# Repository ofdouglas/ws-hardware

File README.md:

# WireSpaces hardware

Status: draft · Owner: project maintainer · Updated: 2026-09-06

Hardware experiments for WireSpaces (WS), starting with a small four-MCU bench board. This repository is a design scaffold, not a fabrication release. Board1 has a complete draft KiCad schematic, reconciled counts and [initial unrouted PCB placement](boards/board1/kicad/placement.md). Schematic approval, detailed placement/routing and hardware qualification remain. This is not a validated fabrication or ordering package.

## Start here

1. Read [agent instructions](AGENTS.md) and [document/decision conventions](docs/DESIGN_PRINCIPLES.md).
2. Read [system context](docs/WIRESPACES_SYSTEM_CONTEXT.md) and [family architecture](docs/HARDWARE_ARCHITECTURE.md).
3. Check the [ADR index](docs/decisions/README.md) before changing a decision.
4. Work from [Board 1 requirements](boards/board1/requirements.md), then its [current design overview](boards/board1/README.md), [pinmap](boards/board1/pinmap.md) and [BOM](boards/board1/bom_internal.csv).

```text
ws-hardware/
├── AGENTS.md
├── README.md
├── docs/
│   ├── WIRESPACES_SYSTEM_CONTEXT.md
│   ├── HARDWARE_ARCHITECTURE.md
│   ├── DESIGN_PRINCIPLES.md
│   ├── PART_SELECTION_POLICY.md
│   ├── SOURCE_NOTES.md
│   └── decisions/                 # index, template, numbered ADRs
├── boards/board1/
│   ├── README.md
│   ├── requirements.md
│   ├── pinmap.md
│   ├── bom_internal.csv
│   └── kicad/                    # board CAD workspace; see board status
└── libraries/
    ├── symbols/
    └── footprints/
```

Board 1's Rev A networking scope has one STM32 gateway, three SAM leaves, two shared CAN-FD buses, an onboard multidrop UART, a private SAM UART ring, USB power/VCP, one external RS-485, signal terminals for both CANs and RS-485 with ground, and debug access. The full bench backbone is future work. Exact MVP inclusion is controlled by the requirements status rows, not by this overview.

Use **Host**, `HostId`, `SrcHostId`, and `DestHostId`. A PC is a PC/test controller; a WS Host is a protocol identity and need not be a PC.

See [source provenance](docs/SOURCE_NOTES.md). Source drafts provide context, not automatic approval for added hardware. Keep small, reviewable changes with requirement IDs and evidence. Resolve the blocking questions in Board 1 requirements before schematic freeze.

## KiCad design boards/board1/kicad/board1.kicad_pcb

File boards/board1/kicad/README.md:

# Board 1 KiCad project — complete schematic and initial PCB placement

Gateway correction (2026-09-07): STM32G473RBT6 is selected and captured per [ADR-043](../../../docs/decisions/043-gateway-part-correction.md). DS12288 references and older workbook/PDF snapshots below are prior G474 evidence, not G473 qualification. Recheck exact G473 AF/electrical limits under B1-Q005/008 before schematic approval.

Completed 2026-09-07 with KiCad 7.0.11, native schematic format20230121, revision A-draft. Open [board1.kicad_pro](board1.kicad_pro). The editable source is the authority for implemented connectivity. The [native PCB](board1.kicad_pcb) now has all components approximately placed, with no tracks, vias or zones. See [placement notes and checks](placement.md) and the [preview](review/board1-initial-placement.png). The outline and placement are provisional; no fabrication outputs have been created.

| Page | Source | Contents |
|---|---|---|
| 1 | [Overview](board1.kicad_sch) | Hierarchy and scope |
| 2 | [Power](power.kicad_sch) | Preserved USB input/ramp, buck, enable and power LED |
| 3 | [USB](usb_bridge.kicad_sch) | Preserved FTDI/EEPROM and four-channel VCP isolation |
| 4 | [Gateway](gateway.kicad_sch) | STM32G473, supplies, crystal, reset/BOOT0, SWD and timing/debug |
| 5–7 | [SAM0](sam0.kicad_sch), [SAM1](sam1.kicad_sch), [SAM2](sam2.kicad_sch) | Three independent SAMC21 circuits and headers |
| 8–9 | [CAN A](can_a.kicad_sch), [CAN B](can_b.kicad_sch) | Eight PHYs, per-PHY standby defaults and endpoint termination |
| 10 | [Interfaces](interfaces.kicad_sch) | UART_MD quad driver, RS-485/defaults/bias/termination, shared timing pulls |
| 11 | [Access](access.kicad_sch) | External terminal block, three TVS arrays, six ground headers, twelve test pads and seven communications headers |

[Complete 11-page review PDF](review/board1-complete.pdf). The earlier two-page power/USB PDF and capture_manifest.json are retained as historical capture evidence; the complete PDF is also an older capture snapshot. Use native schematic files and [complete_manifest.json](complete_manifest.json) for current review. The revised access page is available as [SVG](review/board1-access.svg).

## Capture and component reconciliation

239 schematic component objects comprise 227 fitted components/connectors and 12 PCB copper test pads; two removable CAN shunts are assembly accessories without additional PCB footprints. The strip-stock purchase and testpad/shunt exceptions are explicit in [schematic_bom_allocations.json](schematic_bom_allocations.json). All populated components have MPNs, references and footprint assignments in [bom_internal.csv](../bom_internal.csv); no count remains TBD. Evidence status stays unverified until the relevant approval checks finish.

The original 52 power/USB components retain their pin mappings, MPNs and values. Only hierarchy and the VBUS_RAW global name scope changed. The four GW_VCP nets now reach the gateway.

PCB spacing follow-up: the SAM timing headers are farther from the terminal,
the lower IC groups use more of the lower-right area, and every testpad has
function silkscreen and nearby ground access. See [test access](placement.md#test-access).

Routine completion choices: four reset pull-ups, three SAM SWCLK pull-ups and gateway BOOT0 pull-down use10k B080; NRST uses100n B081 and each SAM RESET uses10n B082. Eight10k CAN STB pull-ups B083 establish explicit standby. Four RS-485 defaults B023 establish shutdown/idle, and four debug RX10k pull-ups B060 establish idle. These reuse selected MPNs; they are engineering choices within authorized scope, not newly maintainer-accepted decisions. No automatic CBUS recovery or future circuitry was added.

Each timing/debug header has six independent330ohm branches near its MCU. Shared SYNC/TRIG each have one10k pull-down before fanout. Six separately purchased two-pin ground headers reuse PRPC002SAAN-RC and do not consume the eight spare positions in the timing-header strip.

B036 reconciles to37 actual main-rail100n bypasses; two unused planning reserves were removed. Main nominal capacitance becomes34.41uF. B007/B010 residual aggregates now have zero parts; B023 andB060 are fully enumerated. [Decoupling](../decoupling.md) and the generated BOM use the captured counts.

## Evidence and corrections

The MCU review found and fixed an actual workbook error in STM32 pads19–29: LED PA5 is pad19, VSSA pad27, VREF+ pad28 and VDDA pad29. Stable physical-pad IDs were retained. [Pinmap](../pinmap.md) links the corrected workbook and [MCU capture plan](../mcu_capture_plan.json). All208 MCU pads were independently compared to that plan/workbook and a fresh KiCad netlist. Timing interrupts are GWPC0/PC1 EXTI0/1 and SAMPA02/PA03 EXTINT2/3; events use GWPC2/PC3 and SAMPB08/PB09.

The RS-485 RO-to-PC11 high-level screen passes: ST3485 VOH>=2.0V at4mA; PC11 FT_f supports alternate guaranteed VIH=0.49VDD+0.26, at most1.9015V with3.35V main DC rail (ST DS12288Rev6 Table54pp128–129). This is a static limit comparison, not a measured waveform margin. FTDI-to-LV125 still has the previously recorded55mV high-level DC headroom before ripple/ground error; use short paths and validate12Mbaud at bring-up.

[Footprint checks](footprint_checks.md) record manufacturer-drawing checks and the two new portable connector footprints. All source symbols are embedded. The standard STM32 exact variant is flattened from its KiCad library inheritance without changing its pins. The existing Board1 FT232HL symbol retains corrected VCCD/EECLK/EECS electrical types. PWR_FLAGs are annotations, not physical circuitry.

## Checks and remaining stages

Run `python3 scripts/check_board1_complete.py` from the repository root. It exports native KiCad XML and checks239 objects/879 pins, explicit NCs, fields, exact numbered-pad coverage, all BOM quantities and independent topology rules for MCU ownership, SWD, header branches, ring, UART_MD, CAN polarity/termination/protection, RS-485, separate SAM core rails and preserved power/USB circuitry. The fresh PCB/netlist comparison and independent topology checks pass. The full schematic/BOM check now stops at the preexisting B059 purchased-header MPN mismatch; see placement notes. The older PDF was rendered and reviewed at its original capture stage. Capture scripts are one-time provenance, not the editing authority; do not rerun over subsequent manual CAD edits.

ERC has not run: KiCad7 CLI exposes schematic export but no ERC command. Run Eeschema ERC before schematic approval. PCB DRC was run through the Python API for [initial placement](placement.md#checks-performed); it is not a clean fabrication DRC. Exact assembly/mating, detailed placement and routing remain layout checks. No hardware validation is claimed. The stale ADR-040 research link now points to its verified historical Git revision; the accepted decision text is unchanged. The current document and purchasing audits flag the preexisting B027/B059 purchase reconciliation; see ../digikey_upload_review.md.

Manual bench operating limits: external timing/debug sources must be3.3V, and drive only while3V3_SYS is on; connect after configuration and disconnect before power-off/suspend. Series resistors do not provide power-off isolation. Disable/disconnect the RS-485 peer before local power-off/suspend because the accepted330ohm bias can feed main power. SWD VTref is sense only. First programming uses connect-under-reset with external bus peers disconnected, then firmware establishes PHY defaults. These limits avoid adding automatic isolation to this prototype.

Bring-up: program/read back FTDI EEPROM per [USB VCP](../usb_vcp.md); check current/startup/suspend, MCU reset/boot, crystal start/frequency,12Mbaud VCP and chosen CAN/UART rates. SAM EIC uses synchronous active-run mode; clear flags after enable and heed DS80000740T errata for the fitted revision. Measurements are not draft-capture blockers.

Primary references: [STM32 DS12288](https://www.st.com/resource/en/datasheet/stm32g474rb.pdf), [SAM DS60001479J](https://ww1.microchip.com/downloads/aemDocuments/documents/MCU32/ProductDocuments/DataSheets/SAM-C20-C21-Family-Data-Sheet-DS60001479J.pdf), [TCAN3413](https://www.ti.com/lit/ds/symlink/tcan3413.pdf), [ST3485](https://www.st.com/resource/en/datasheet/st3485eb.pdf), [LV125](https://www.ti.com/lit/ds/symlink/sn74lv125a.pdf), [FT232H v2.2](https://www.ftdichip.cn/Support/Documents/DataSheets/ICs/DS_FT232H.pdf). FTDI current errata/on-hand silicon reconciliation remains an approval check; no retrieved source attachments were edited.

ADR-046 communications access: J19/J20 CAN H,L; J21 RS-485 A,B; J22/J23/J24 ring01/ring12/ring20 signal,GND; J25 UART_MD signal,GND. All are fitted 1×2 0.1-inch headers with function and pin-order silkscreen. TP1–TP12 remain copper pads.

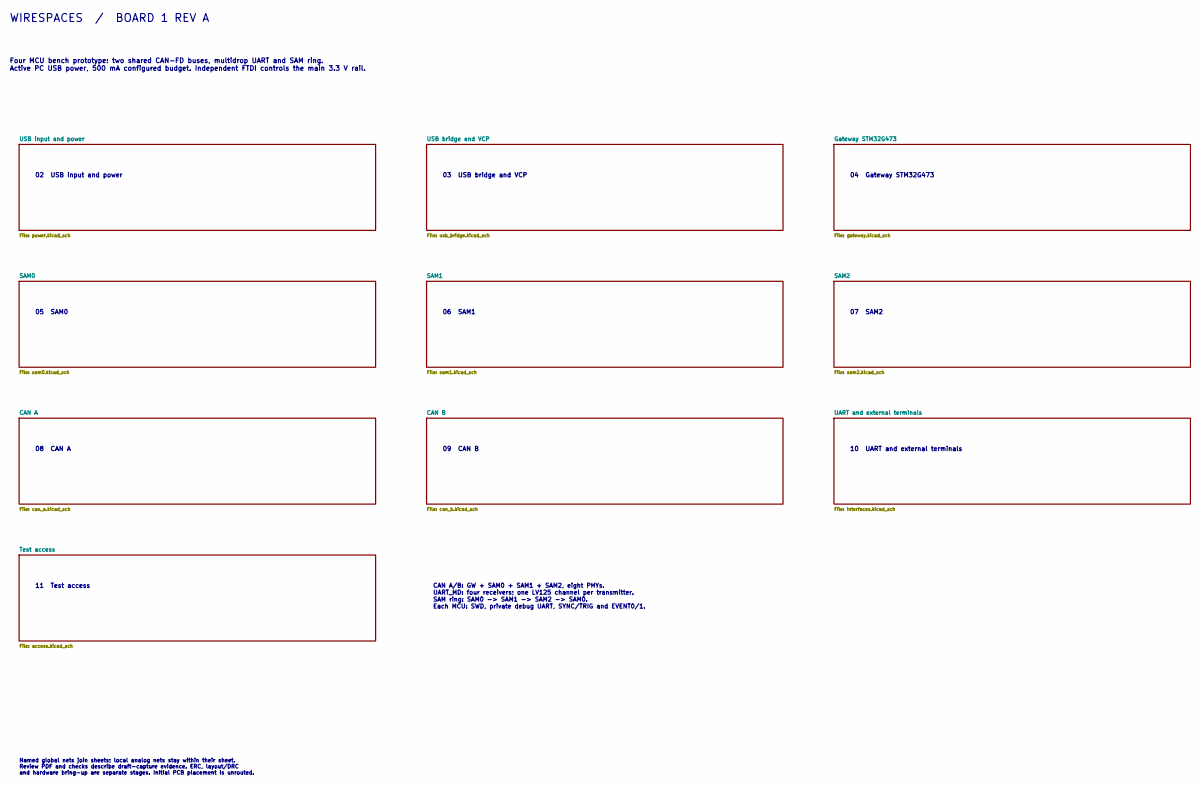
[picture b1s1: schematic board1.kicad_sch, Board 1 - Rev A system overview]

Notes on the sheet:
WIRESPACES / BOARD 1 REV A
Four MCU bench prototype: two shared CAN-FD buses, multidrop UART and SAM ring. Active PC USB power, 500 mA configured budget. Independent FTDI controls the main 3.3 V rail.
02 USB input and power
03 USB bridge and VCP
04 Gateway STM32G473
05 SAM0
06 SAM1
07 SAM2
08 CAN A
09 CAN B
10 UART and external terminals
11 Test access
CAN A/B: GW + SAM0 + SAM1 + SAM2, eight PHYs. UART_MD: four receivers; one LV125 channel per transmitter. SAM ring: SAM0 -> SAM1 -> SAM2 -> SAM0. Each MCU: SWD, private debug UART, SYNC/TRIG and EVENT0/1.
Named global nets join sheets; local analog nets stay within their sheet. Review PDF and checks describe draft-capture evidence. ERC, layout/DRC and hardware bring-up are separate stages. Initial PCB placement is unrouted.

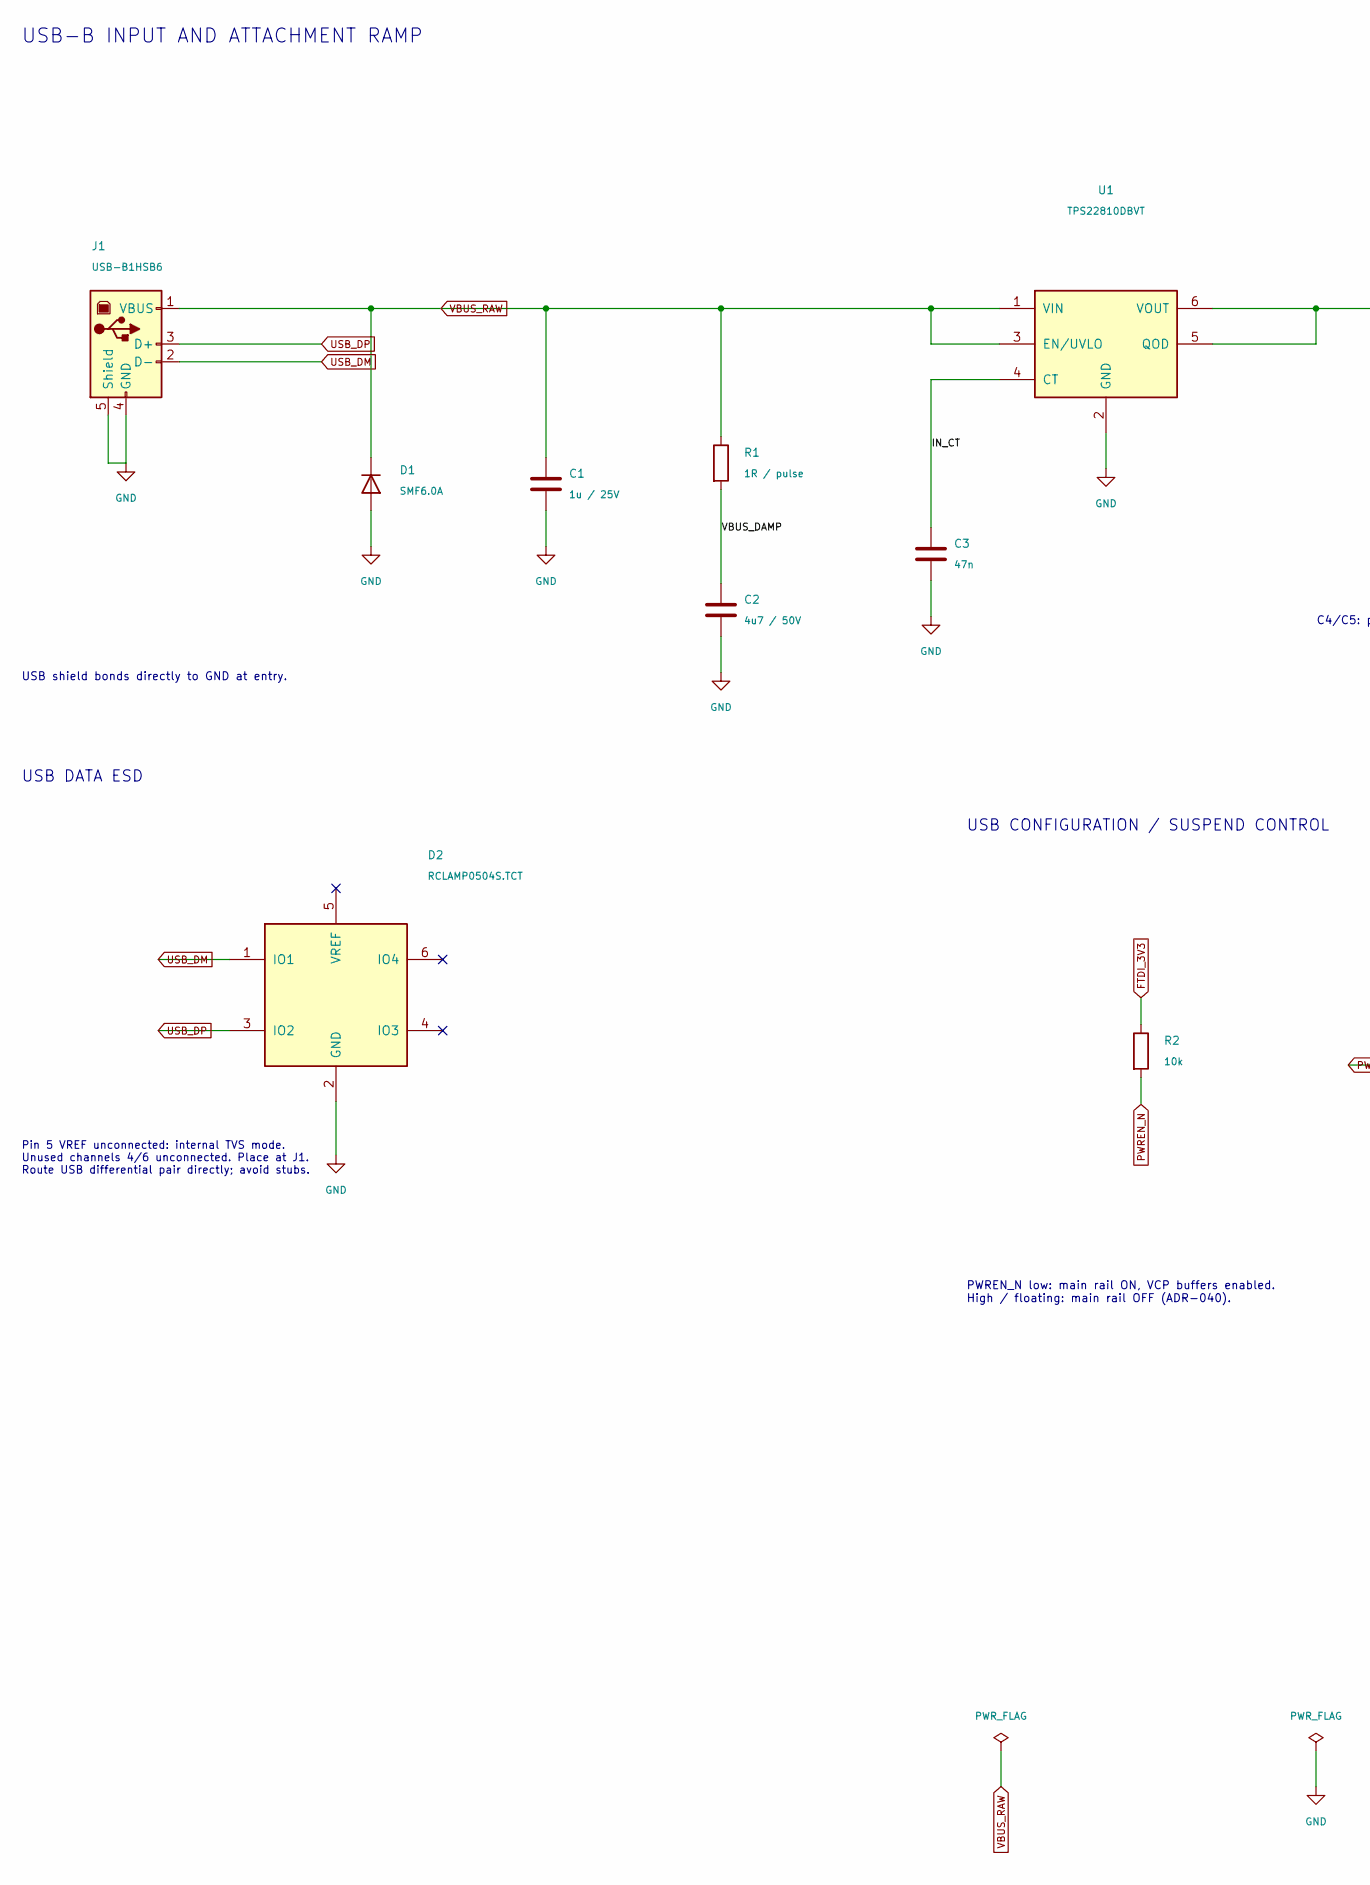
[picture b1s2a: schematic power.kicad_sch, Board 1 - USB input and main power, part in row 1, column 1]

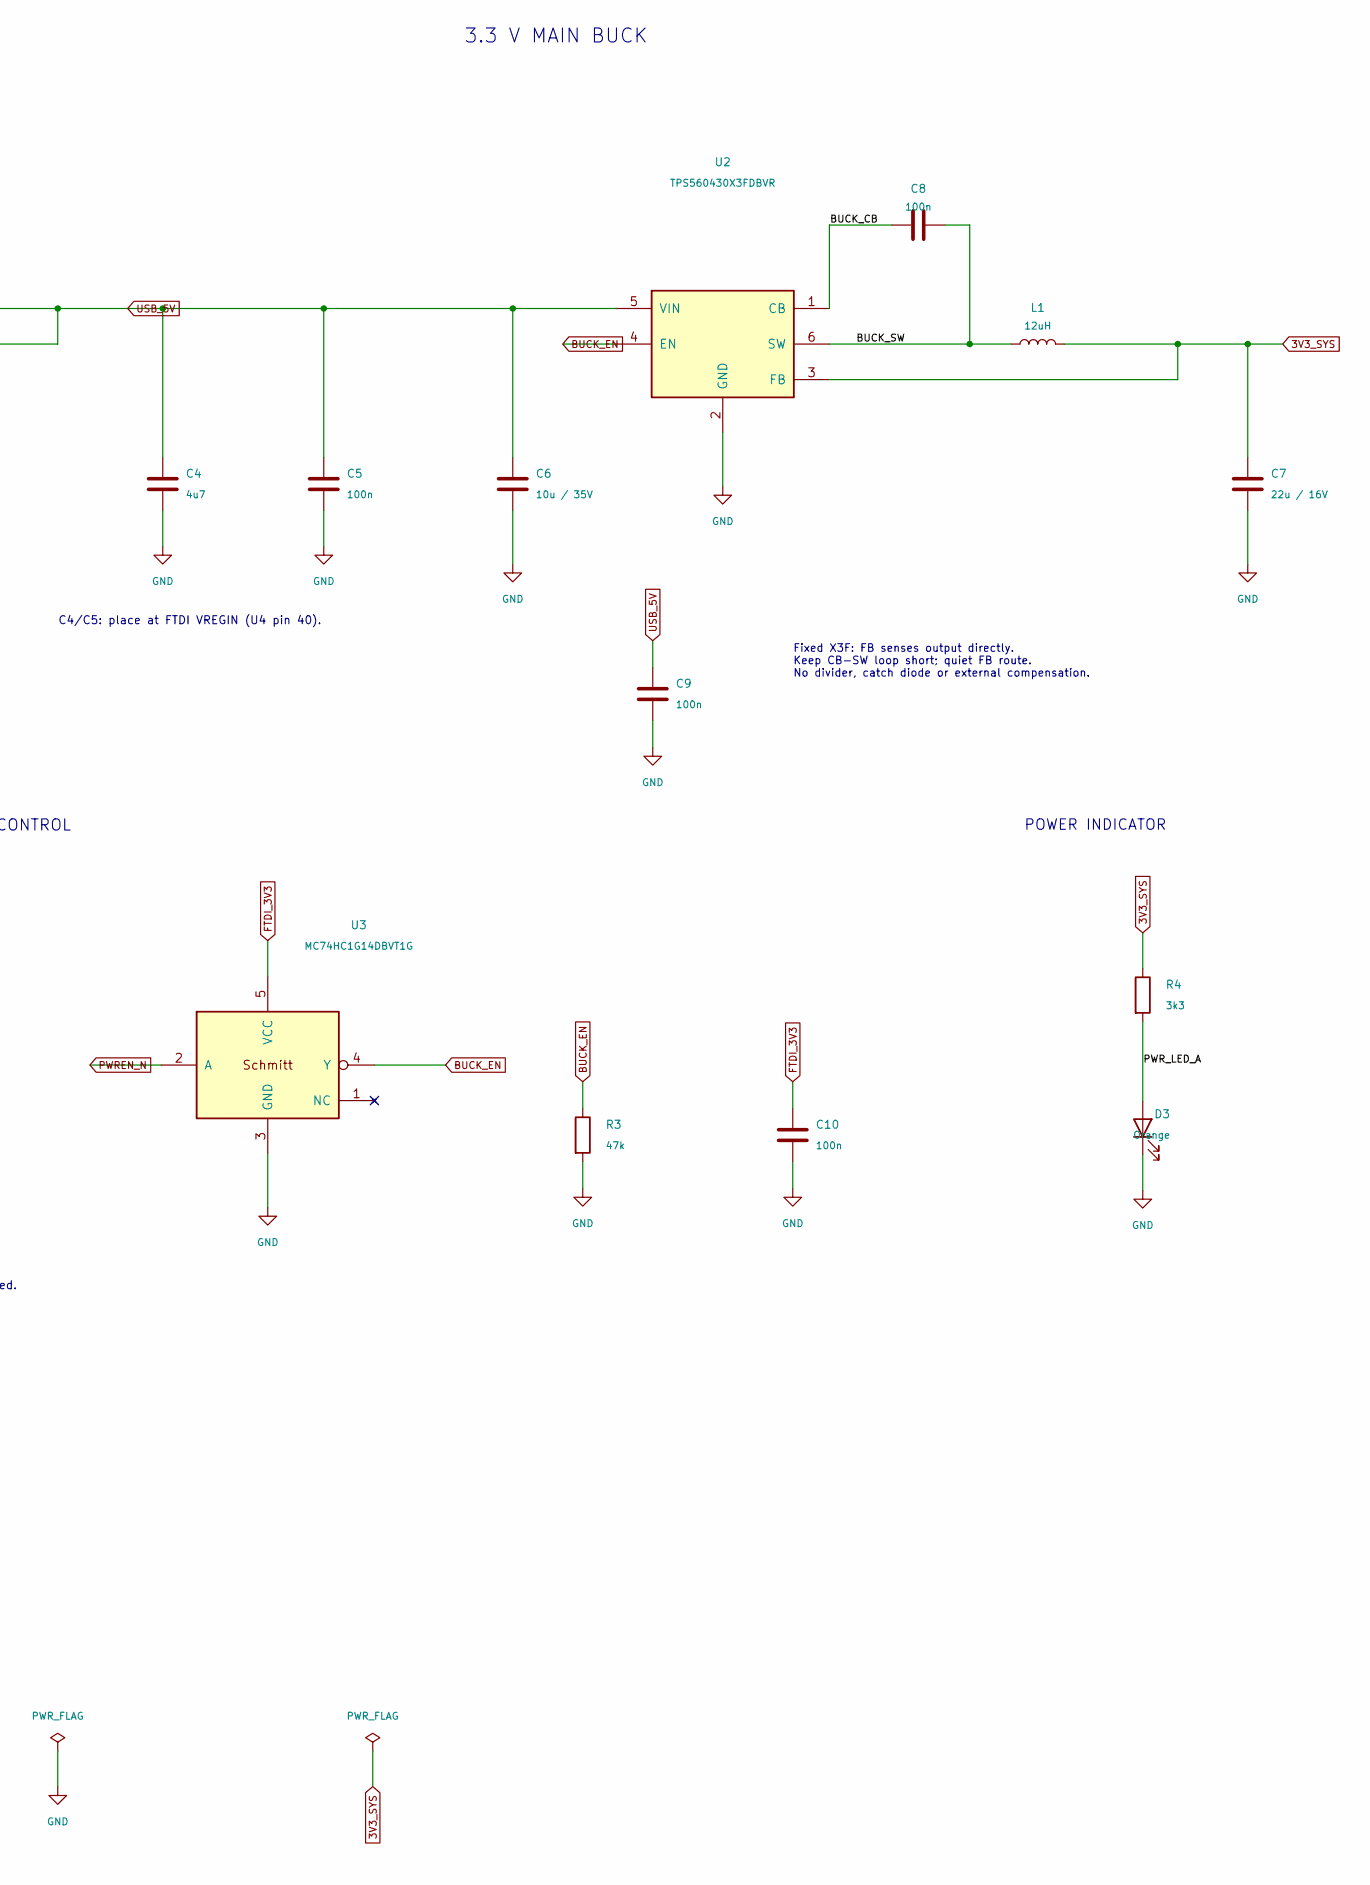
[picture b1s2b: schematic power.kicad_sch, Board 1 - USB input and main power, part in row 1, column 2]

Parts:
C1: 1u / 25V; C_0805_2012Metric; MPN CL21B105KAFNFNE
C2: 4u7 / 50V; C_0805_2012Metric; MPN CL21A475KBQNNNE
C3: 47n; C_0805_2012Metric; MPN CL21B473KBCNNNC
C4: 4u7; C_0805_2012Metric; MPN GRM21BR71C475KE51L
C5, C10: 100n; C_0805_2012Metric; MPN KGM21NR71E104KT
C6: 10u / 35V; C_1206_3216Metric; MPN C3216X7R1V106K160AC
C7: 22u / 16V; C_1210_3225Metric; MPN C3225X7R1C226M250AC
C8, C9: 100n; C_0805_2012Metric; MPN C0805C104K5RACTU
D1: SMF6.0A; D_SOD-123F; MPN SMF6.0A
D2: RCLAMP0504S.TCT; SOT-23-6; MPN RCLAMP0504S.TCT
D3: Orange; LED_0603_1608Metric; MPN CSL1901DW1
J1: USB-B1HSB6; USB_B_OST_USB-B1HSxx_Horizontal; MPN USB-B1HSB6
L1: 12uH; L_Bourns_SRN6045TA; MPN SRN6045TA-120M
R1: 1R / pulse; R_1206_3216Metric; MPN SG73P2BTTD1R0J
R2: 10k; R_0805_2012Metric; MPN RMCF0805FT10K0
R3: 47k; R_0805_2012Metric; MPN ERJ-6GEYJ473V
R4: 3k3; R_0805_2012Metric; MPN RK73H2ATTD3301F
U1: TPS22810DBVT; SOT-23-6; MPN TPS22810DBVT
U2: TPS560430X3FDBVR; SOT-23-6; MPN TPS560430X3FDBVR
U3: MC74HC1G14DBVT1G; SOT-23-5; MPN MC74HC1G14DBVT1G

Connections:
3V3_SYS: C7.1, L1.2, R4.1, U2.3 (FB); also elsewhere on the board
/USB input and power/BUCK_CB: C8.1, U2.1 (CB)
/USB input and power/BUCK_SW: C8.2, L1.1, U2.6 (SW)
/USB input and power/IN_CT: C3.1, U1.4 (CT)
/USB input and power/PWR_LED_A: D3.2 (A), R4.2
/USB input and power/VBUS_DAMP: C2.1, R1.2
BUCK_EN: R3.1, U2.4 (EN), U3.4 (Y)
FTDI_3V3: C10.1, R2.1, U3.5 (VCC); also elsewhere on the board
GND: C1.2, C2.2, C3.2, C4.2, C5.2, C6.2, C7.2, C9.2, C10.2, D1.2 (A), D2.2 (GND), D3.1 (K), J1.4 (GND), J1.5 (Shield), R3.2, U1.2 (GND), U2.2 (GND), U3.3 (GND); also elsewhere on the board
PWREN_N: R2.2, U3.2 (A); also elsewhere on the board
USB_5V: C4.1, C5.1, C6.1, C9.1, U1.5 (QOD), U1.6 (VOUT), U2.5 (VIN); also elsewhere on the board
USB_DM: D2.1 (IO1), J1.2 (D-); also elsewhere on the board
USB_DP: D2.3 (IO2), J1.3 (D+); also elsewhere on the board
VBUS_RAW: C1.1, D1.1 (K), J1.1 (VBUS), R1.1, U1.1 (VIN), U1.3 (EN/UVLO); also elsewhere on the board

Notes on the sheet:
USB-B INPUT AND ATTACHMENT RAMP
3.3 V MAIN BUCK
C4/C5: place at FTDI VREGIN (U4 pin 40).
USB shield bonds directly to GND at entry.
USB DATA ESD
Pin 5 VREF unconnected: internal TVS mode. Unused channels 4/6 unconnected. Place at J1. Route USB differential pair directly; avoid stubs.
Fixed X3F: FB senses output directly. Keep CB-SW loop short; quiet FB route. No divider, catch diode or external compensation.
USB CONFIGURATION / SUSPEND CONTROL
PWREN_N low: main rail ON, VCP buffers enabled. High / floating: main rail OFF (ADR-040).
POWER INDICATOR

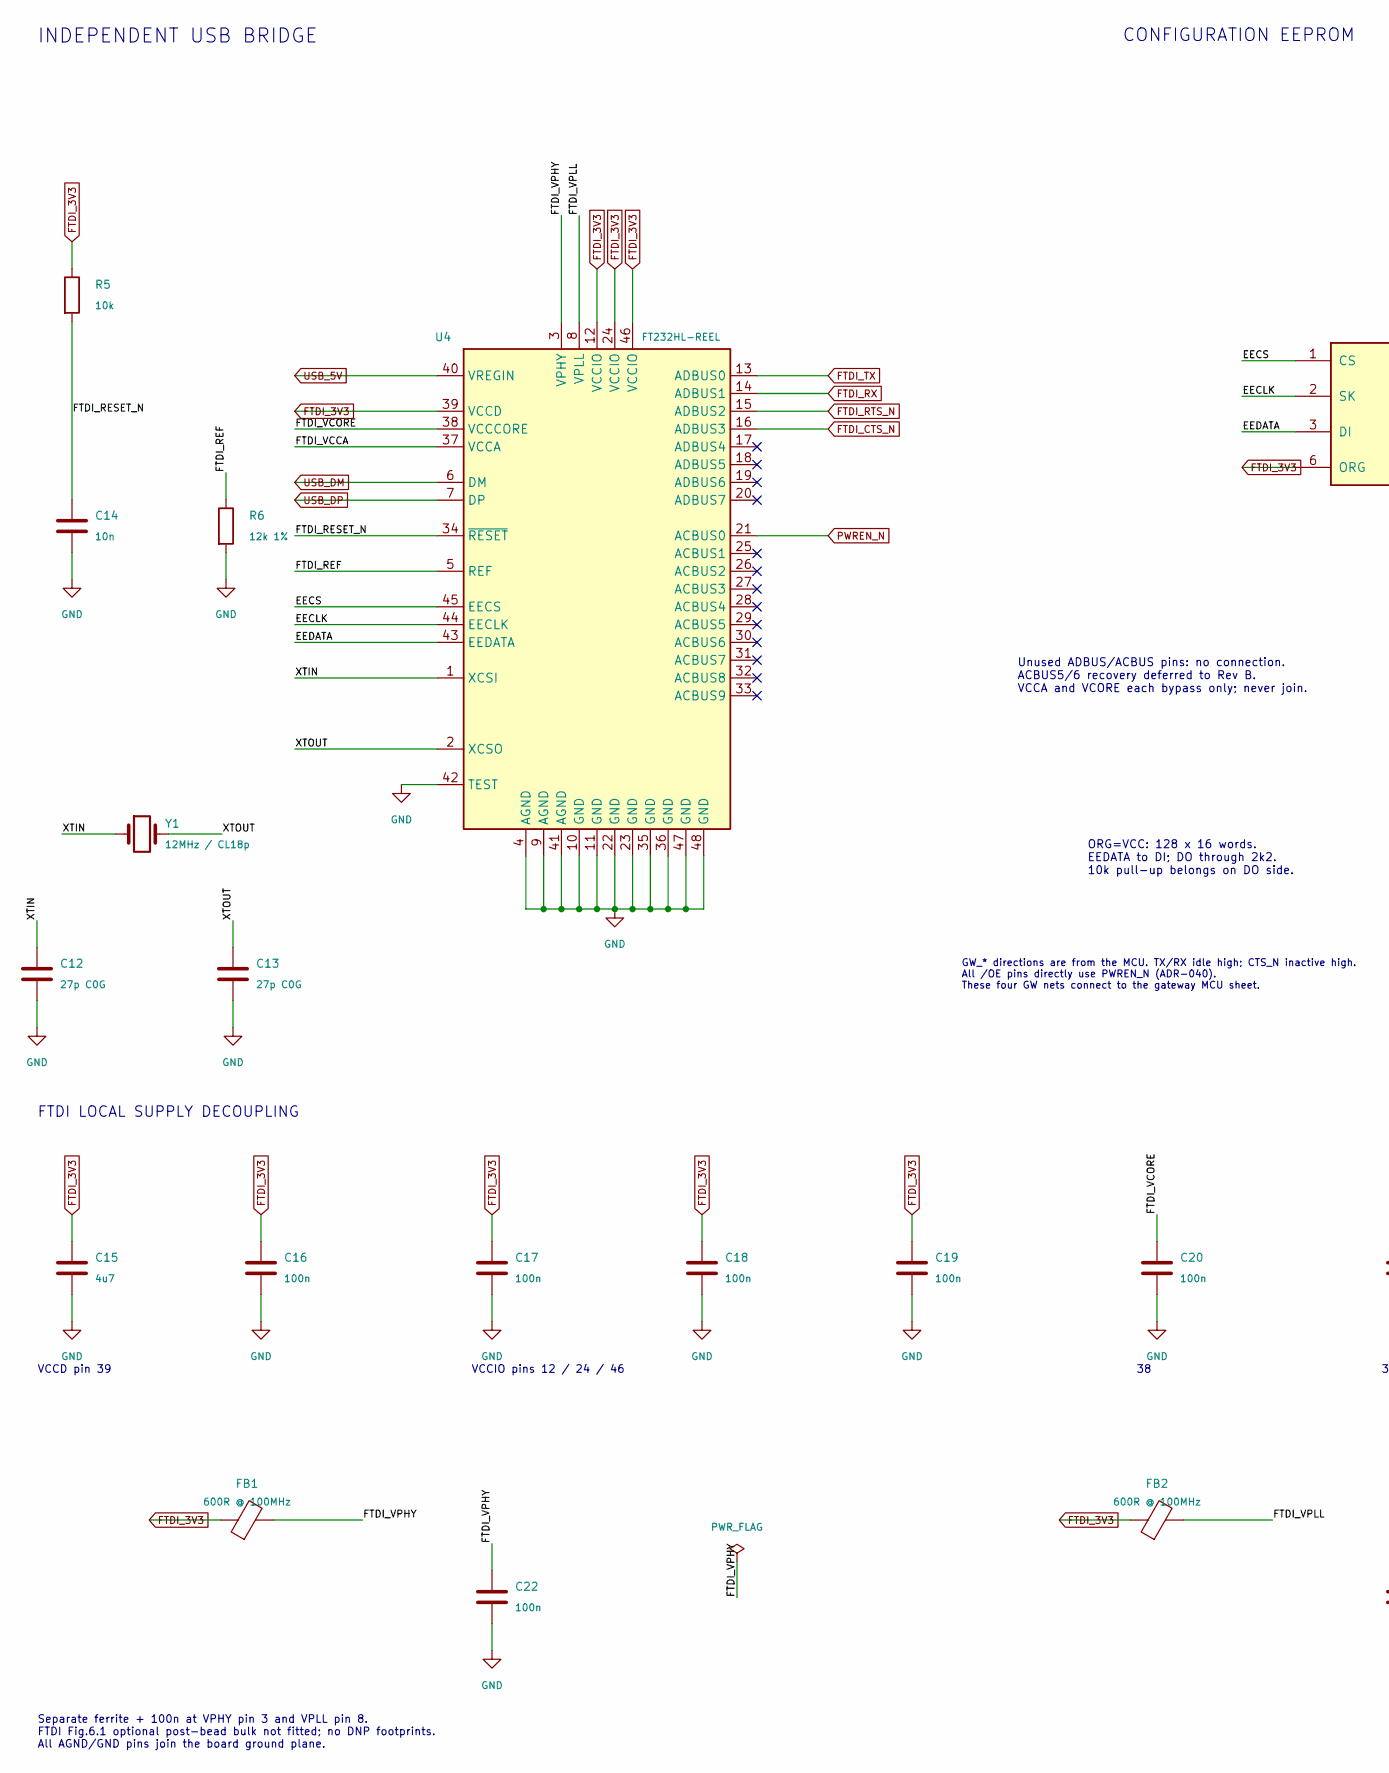
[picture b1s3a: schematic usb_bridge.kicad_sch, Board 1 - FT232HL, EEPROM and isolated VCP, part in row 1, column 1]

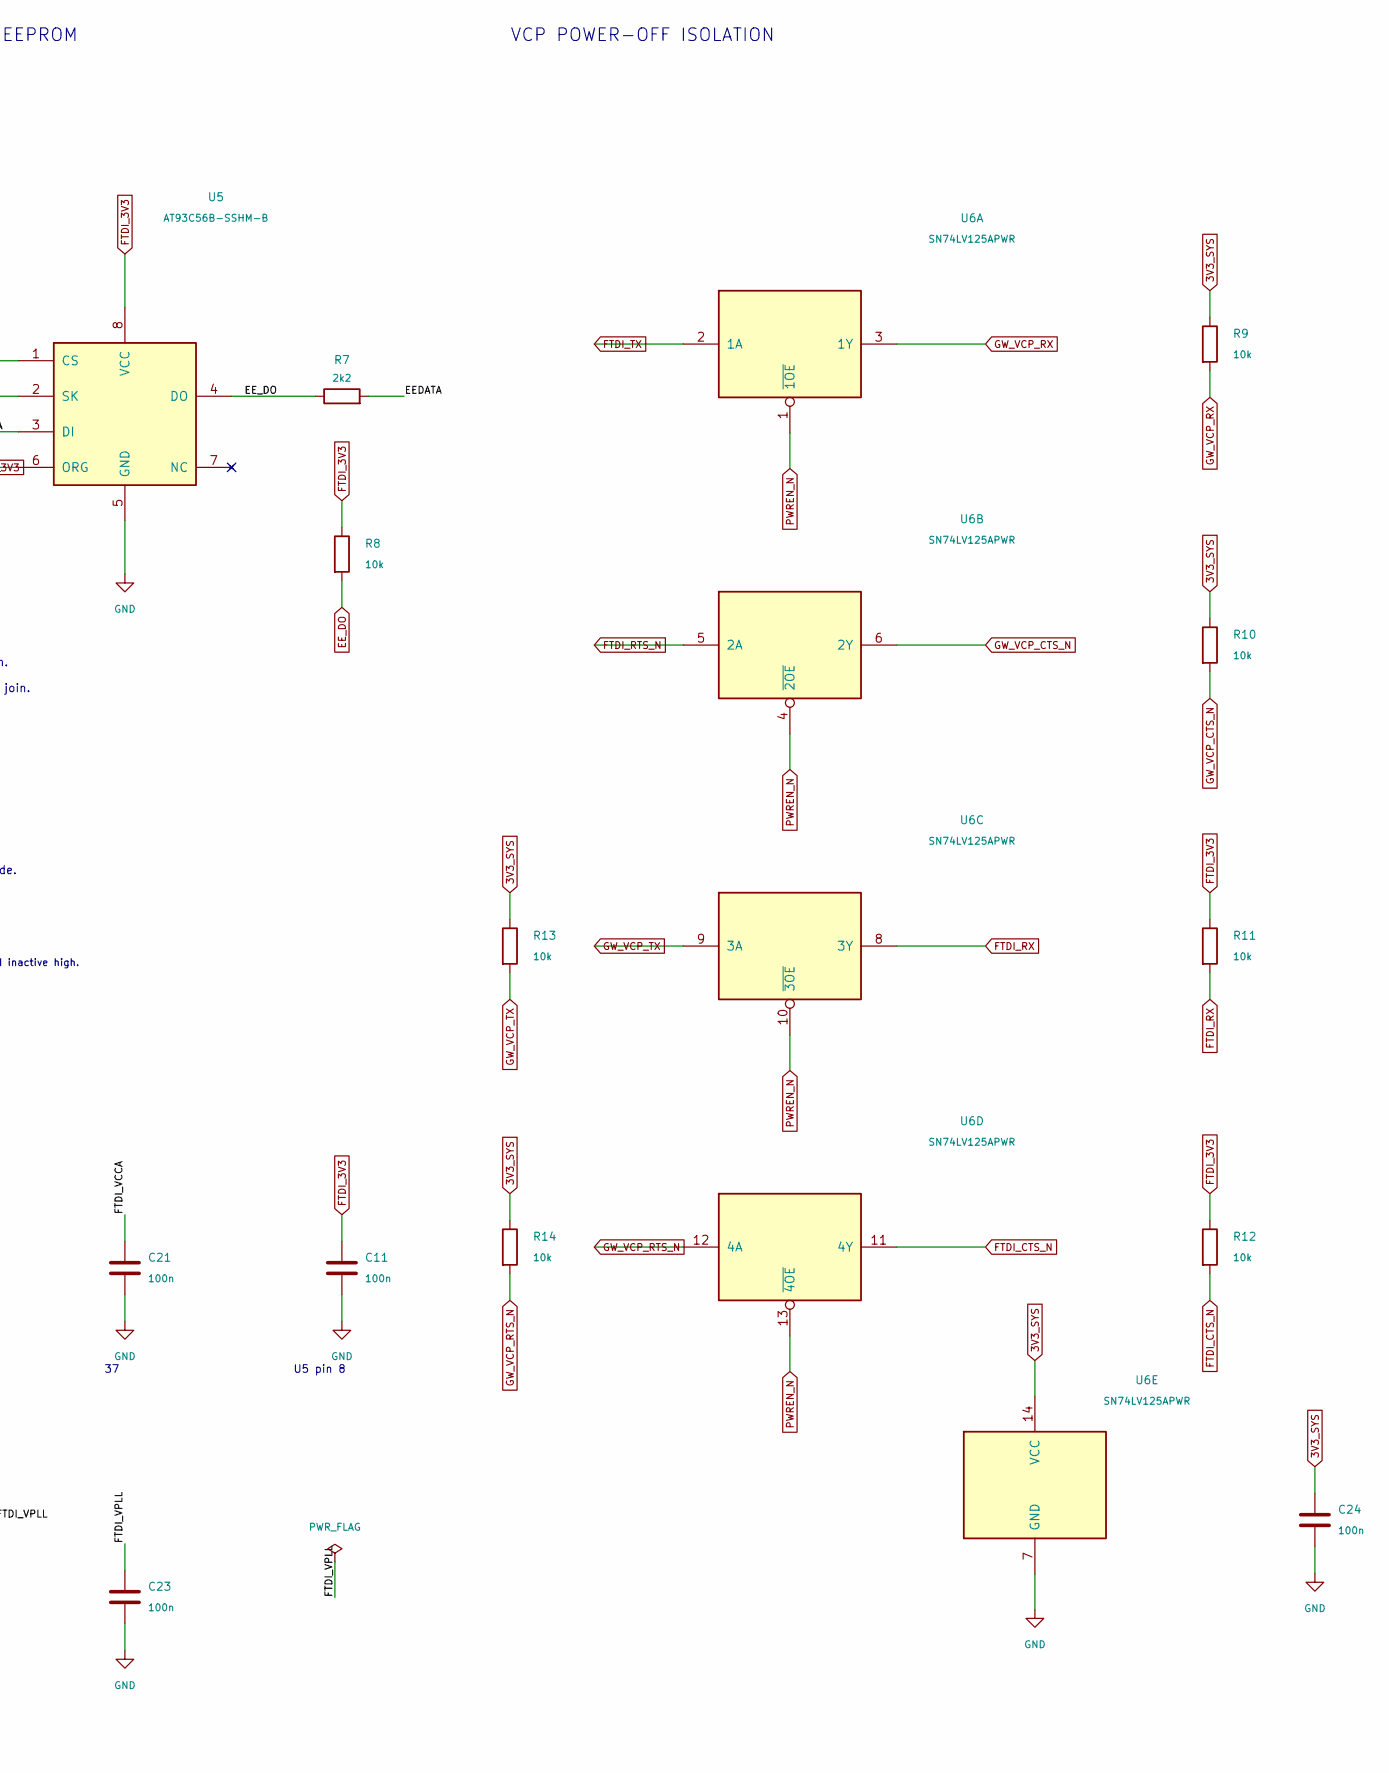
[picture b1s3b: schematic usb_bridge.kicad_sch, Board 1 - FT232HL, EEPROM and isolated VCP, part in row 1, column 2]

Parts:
C11, C16, C17, C18, C19, C20, C21, C22, C23, C24: 100n; C_0805_2012Metric; MPN KGM21NR71E104KT
C12, C13: 27p C0G; C_0805_2012Metric; MPN CC0805FRNPO9BN270
C14: 10n; C_0805_2012Metric; MPN CL21B103KBANNNC
C15: 4u7; C_0805_2012Metric; MPN GRM21BR71C475KE51L
FB1, FB2: 600R @ 100MHz; L_0805_2012Metric; MPN BLM21AG601SN1D
R5, R8, R9, R10, R11, R12, R13, R14: 10k; R_0805_2012Metric; MPN RMCF0805FT10K0
R6: 12k 1%; R_0805_2012Metric; MPN RMCF0805FT12K0
R7: 2k2; R_0805_2012Metric; MPN RC0805FR-072K2L
U4: FT232HL-REEL; LQFP-48_7x7mm_P0.5mm; MPN FT232HL-REEL
U5: AT93C56B-SSHM-B; SOIC-8_3.9x4.9mm_P1.27mm; MPN AT93C56B-SSHM-B
U6: SN74LV125APWR; TSSOP-14_4.4x5mm_P0.65mm; MPN SN74LV125APWR
Y1: 12MHz / CL18p; Crystal_SMD_HC49-SD; MPN ECS-120-18-5PX-CKM-TR

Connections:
3V3_SYS: C24.1, R9.1, R10.1, R13.1, R14.1, U6.14 (VCC); also elsewhere on the board
/USB bridge and VCP/EECLK: U4.44 (EECLK), U5.2 (SK)
/USB bridge and VCP/EECS: U4.45 (EECS), U5.1 (CS)
/USB bridge and VCP/EEDATA: R7.2, U4.43 (EEDATA), U5.3 (DI)
/USB bridge and VCP/FTDI_REF: R6.1, U4.5 (REF)
/USB bridge and VCP/FTDI_RESET_N: C14.1, R5.2, U4.34 (~RESET)
/USB bridge and VCP/FTDI_VCCA: C21.1, U4.37 (VCCA)
/USB bridge and VCP/FTDI_VCORE: C20.1, U4.38 (VCCCORE)
/USB bridge and VCP/FTDI_VPHY: C22.1, FB1.2, U4.3 (VPHY)
/USB bridge and VCP/FTDI_VPLL: C23.1, FB2.2, U4.8 (VPLL)
/USB bridge and VCP/XTIN: C12.1, U4.1 (XCSI), Y1.1
/USB bridge and VCP/XTOUT: C13.1, U4.2 (XCSO), Y1.2
EE_DO: R7.1, R8.2, U5.4 (DO)
FTDI_3V3: C11.1, C15.1, C16.1, C17.1, C18.1, C19.1, FB1.1, FB2.1, R5.1, R8.1, R11.1, R12.1, U4.12 (VCCIO), U4.24 (VCCIO), U4.39 (VCCD), U4.46 (VCCIO), U5.6 (ORG), U5.8 (VCC); also elsewhere on the board
FTDI_CTS_N: R12.2, U4.16 (ADBUS3), U6.11 (4Y)
FTDI_RTS_N: U4.15 (ADBUS2), U6.5 (2A)
FTDI_RX: R11.2, U4.14 (ADBUS1), U6.8 (3Y)
FTDI_TX: U4.13 (ADBUS0), U6.2 (1A)
GND: C11.2, C12.2, C13.2, C14.2, C15.2, C16.2, C17.2, C18.2, C19.2, C20.2, C21.2, C22.2, C23.2, C24.2, R6.2, U4.4 (AGND), U4.9 (AGND), U4.10 (GND), U4.11 (GND), U4.22 (GND), U4.23 (GND), U4.35 (GND), U4.36 (GND), U4.41 (AGND), U4.42 (TEST), U4.47 (GND), U4.48 (GND), U5.5 (GND), U6.7 (GND); also elsewhere on the board
GW_VCP_CTS_N: R10.2, U6.6 (2Y); also elsewhere on the board
GW_VCP_RTS_N: R14.2, U6.12 (4A); also elsewhere on the board
GW_VCP_RX: R9.2, U6.3 (1Y); also elsewhere on the board
GW_VCP_TX: R13.2, U6.9 (3A); also elsewhere on the board
PWREN_N: U4.21 (ACBUS0), U6.1 (~1OE), U6.4 (~2OE), U6.10 (~3OE), U6.13 (~4OE); also elsewhere on the board
USB_5V: U4.40 (VREGIN); also elsewhere on the board
USB_DM: U4.6 (DM); also elsewhere on the board
USB_DP: U4.7 (DP); also elsewhere on the board

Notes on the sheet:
INDEPENDENT USB BRIDGE
CONFIGURATION EEPROM
VCP POWER-OFF ISOLATION
Unused ADBUS/ACBUS pins: no connection. ACBUS5/6 recovery deferred to Rev B. VCCA and VCORE each bypass only; never join.
ORG=VCC: 128 x 16 words. EEDATA to DI; DO through 2k2. 10k pull-up belongs on DO side.
FTDI LOCAL SUPPLY DECOUPLING
VCCD pin 39
VCCIO pins 12 / 24 / 46
U5 pin 8
Separate ferrite + 100n at VPHY pin 3 and VPLL pin 8. FTDI Fig.6.1 optional post-bead bulk not fitted; no DNP footprints. All AGND/GND pins join the board ground plane.
GW_* directions are from the MCU. TX/RX idle high; CTS_N inactive high. All /OE pins directly use PWREN_N (ADR-040). These four GW nets connect to the gateway MCU sheet.
